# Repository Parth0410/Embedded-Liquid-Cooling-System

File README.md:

# Embedded-Liquid-Cooling-System
To maintain the Temperature of the water in the bottle.

About this Project:-

The Peltier Tile is the module which has two sides, one becomes cold and other heats up on applying the certain voltage. The main Objective of the project is to make a Liquid Cooler using a Peltier Tile. In this, the base is created which has the Microcontroller, Cooling Fan, and the Temperature sensors which continuously detects and display the temperature of the water as well as of the base in the display.  
As the temp. of water reaches the threshold level i.e., 15 ºC, the Fan and Peltier Tile stops working, and as the temp. again reaches above the threshold i.e., 25 ºC, both again starts working. This will help the battery to work for long duration and resulting the Water remains Cool.

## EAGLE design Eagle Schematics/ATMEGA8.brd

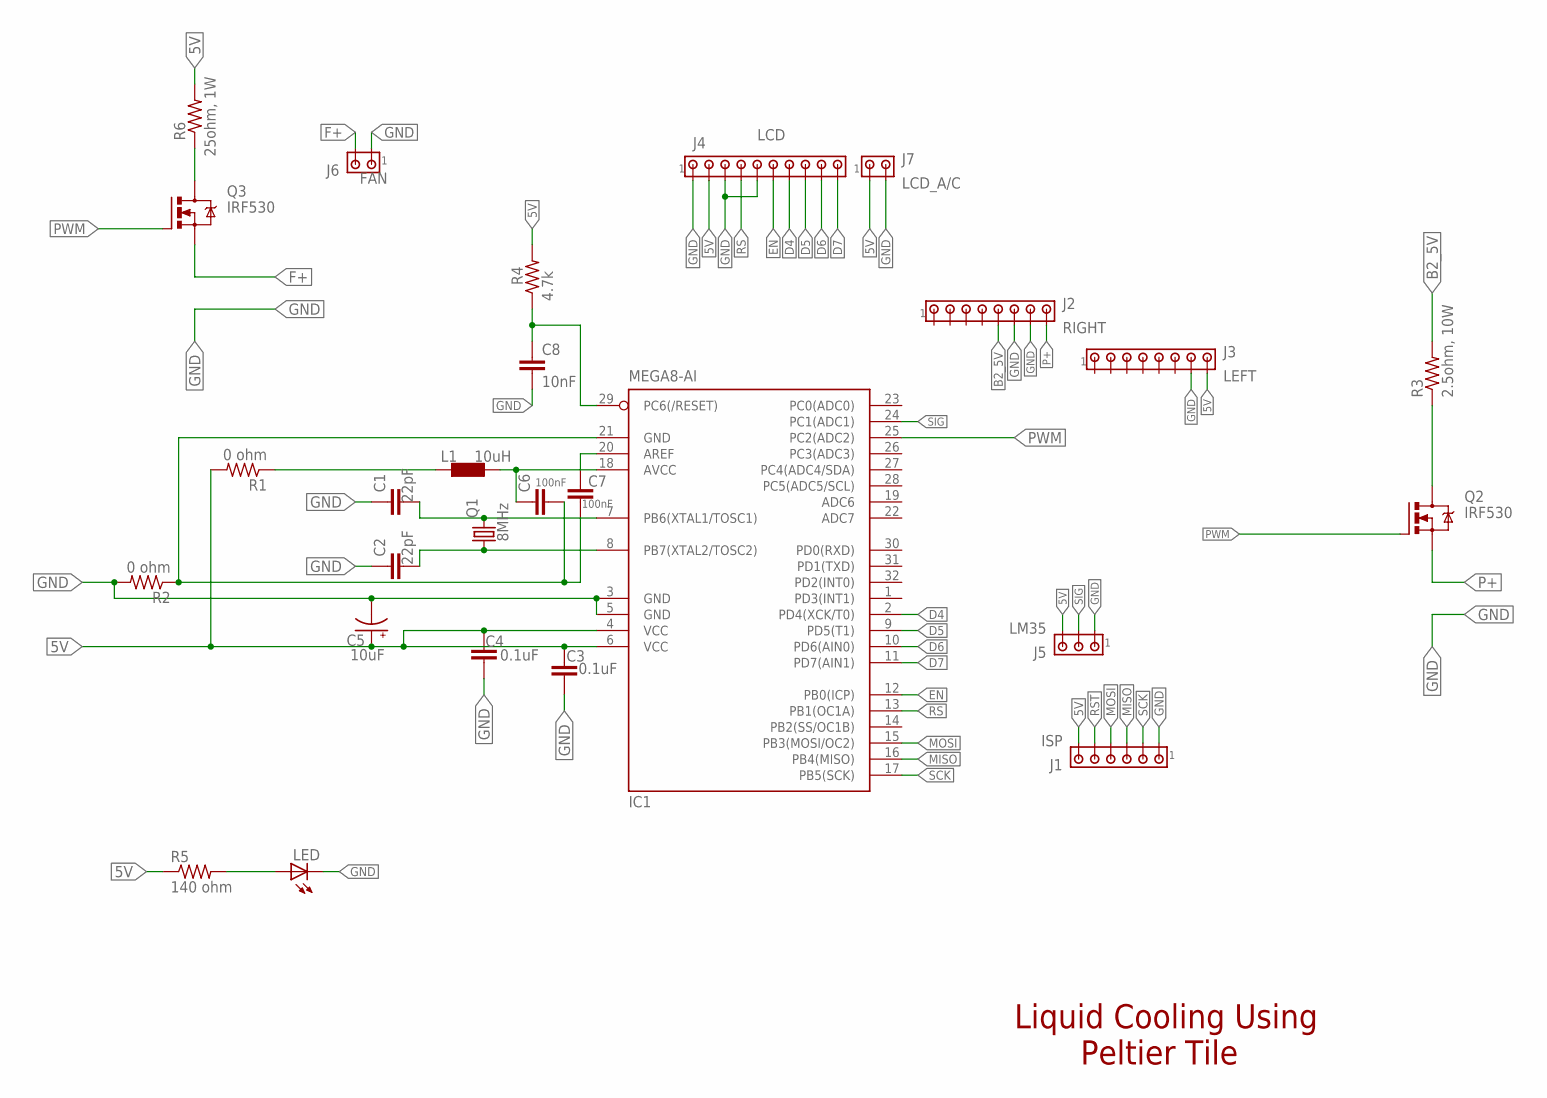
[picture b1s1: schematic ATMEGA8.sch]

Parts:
C1, C2: 22pF; C0805
C3, C4: 0.1uF; C0805
C5: 10uF; A/3216-18R
C6, C7: 100nF; C0805
C8: 10nF; C0805
IC1: MEGA8-AI; TQFP32-08
J1: ISP; 10X06MTA
J2: RIGHT; 10X08MTA
J3: LEFT; 10X08MTA
J4: LCD; 10X10MTA
J5: LM35; 10X03MTA
J6: FAN; 10X02MTA
J7: LCD_A/C; 10X02MTA
L1: 10uH; 0204/7
LED: RED; CHIPLED_1206
Q1: 8MHz; CSM-7X-DU
Q2, Q3: IRF530; TO220BV
R1, R2: 0 ohm; M0805
R3: 2.5ohm, 10W; 0207/9
R4: 4.7k; M0805
R5: 140 ohm; M0805
R6: 25ohm, 1W; 0207/10

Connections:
5V: C3.1, C4.1, C5.+, IC1.4 (VCC), IC1.6 (VCC), J1.6, J3.8, J4.2, J5.3, J7.1, R1.2, R4.2, R5.1, R6.2
B2_5V: J2.5, R3.2
D4: IC1.2 (PD4(XCK/T0)), J4.7
D5: IC1.9 (PD5(T1)), J4.8
D6: IC1.10 (PD6(AIN0)), J4.9
D7: IC1.11 (PD7(AIN1)), J4.10
EN: IC1.12 (PB0(ICP)), J4.6
F+: J6.2, Q3.S
GND: C1.1, C2.1, C3.2, C4.2, C5.-, C8.2, IC1.3 (GND), IC1.5 (GND), J1.1, J2.6, J2.7, J3.7, J4.1, J4.3, J4.5, J5.1, J6.1, J7.2, LED.C, R2.2
MISO: IC1.16 (PB4(MISO)), J1.3
MOSI: IC1.15 (PB3(MOSI/OC2)), J1.4
unnamed: C1.2, IC1.7 (PB6(XTAL1/TOSC1)), Q1.2
unnamed: C2.2, IC1.8 (PB7(XTAL2/TOSC2)), Q1.1
unnamed: C6.1, IC1.18 (AVCC), L1.2
unnamed: Q2.D, R3.1
unnamed: L1.1, R1.1
unnamed: C6.2, C7.2, IC1.21 (GND), R2.1
unnamed: C7.1, IC1.20 (AREF)
unnamed: C8.1, IC1.29 (PC6(/RESET)), R4.1
unnamed: LED.A, R5.2
unnamed: Q3.D, R6.1
P+: J2.8, Q2.S
PWM: IC1.25 (PC2(ADC2)), Q2.G, Q3.G
RS: IC1.13 (PB1(OC1A)), J4.4
RST: J1.5
SCK: IC1.17 (PB5(SCK)), J1.2
SIG: IC1.24 (PC1(ADC1)), J5.2

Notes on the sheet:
Liquid Cooling Using Peltier Tile

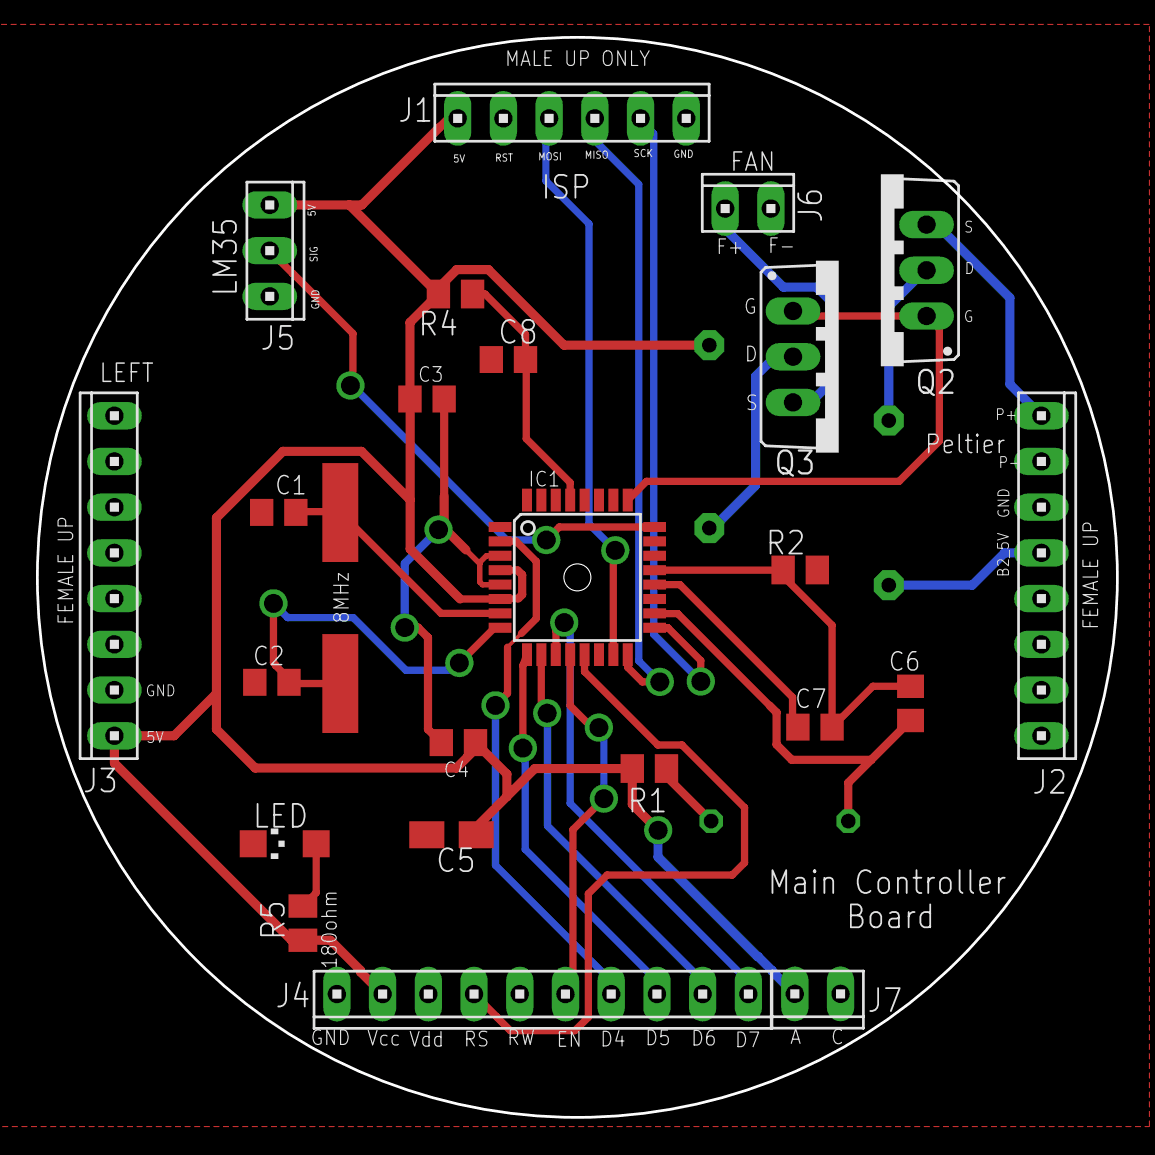
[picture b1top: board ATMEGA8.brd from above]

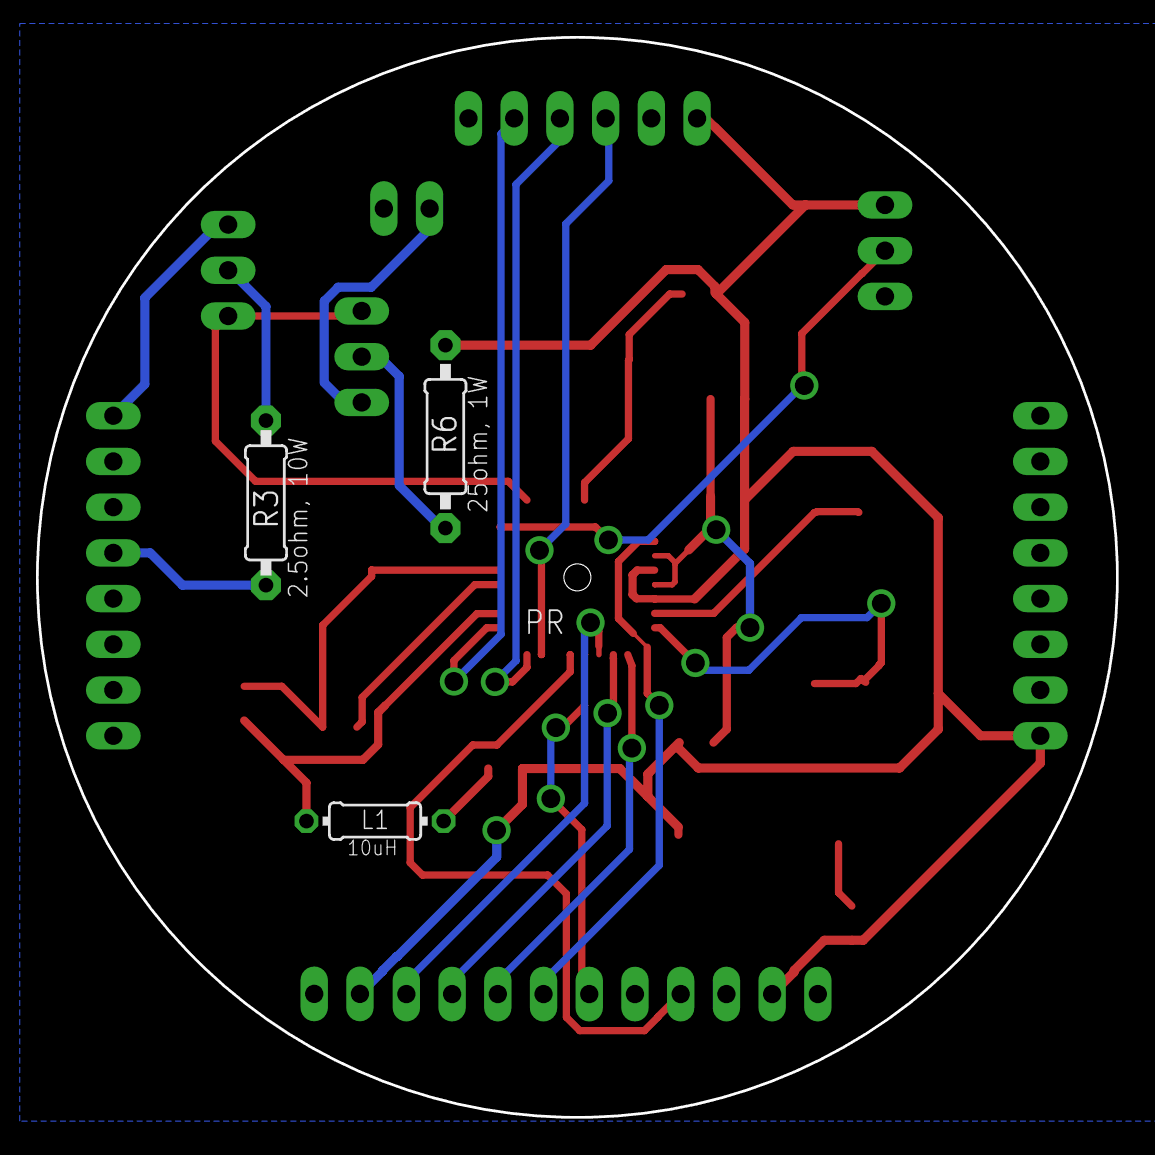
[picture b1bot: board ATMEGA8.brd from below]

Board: 2 copper layers, 60.0 x 60.0 mm, 27 parts (3 on the bottom side), 26 nets.

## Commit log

2019-06-25 Eagle Library
    Required Eagle Library for this Project
2019-06-25 Eagle Library for ADP1613 IC
    Library for Boost Circuit IC
2019-06-25 Atmega8 uC Eagle Library
2019-06-26 Data Sheets that are required
2019-07-25 Add files via upload
    Code for controlling the Peltier and Fan with a threshold.
2019-07-25 Files for Simulation in Proteus
    All the files which are required for the simulation in the Proteus
2019-07-25 Images
    For your reference how the Controller Board looks like.
2019-07-25 Eagle Schematics for Controller Board
    It contains the Eagle Schematic file and Layout file of the Controller Board.
2019-07-25 The Final Abstract of our Project
2019-07-25 Components and Peripherals list
    List of all components and other Peripherals which are needed for the Board.
2019-07-26 Circuit Diagram drawn on Eagle
